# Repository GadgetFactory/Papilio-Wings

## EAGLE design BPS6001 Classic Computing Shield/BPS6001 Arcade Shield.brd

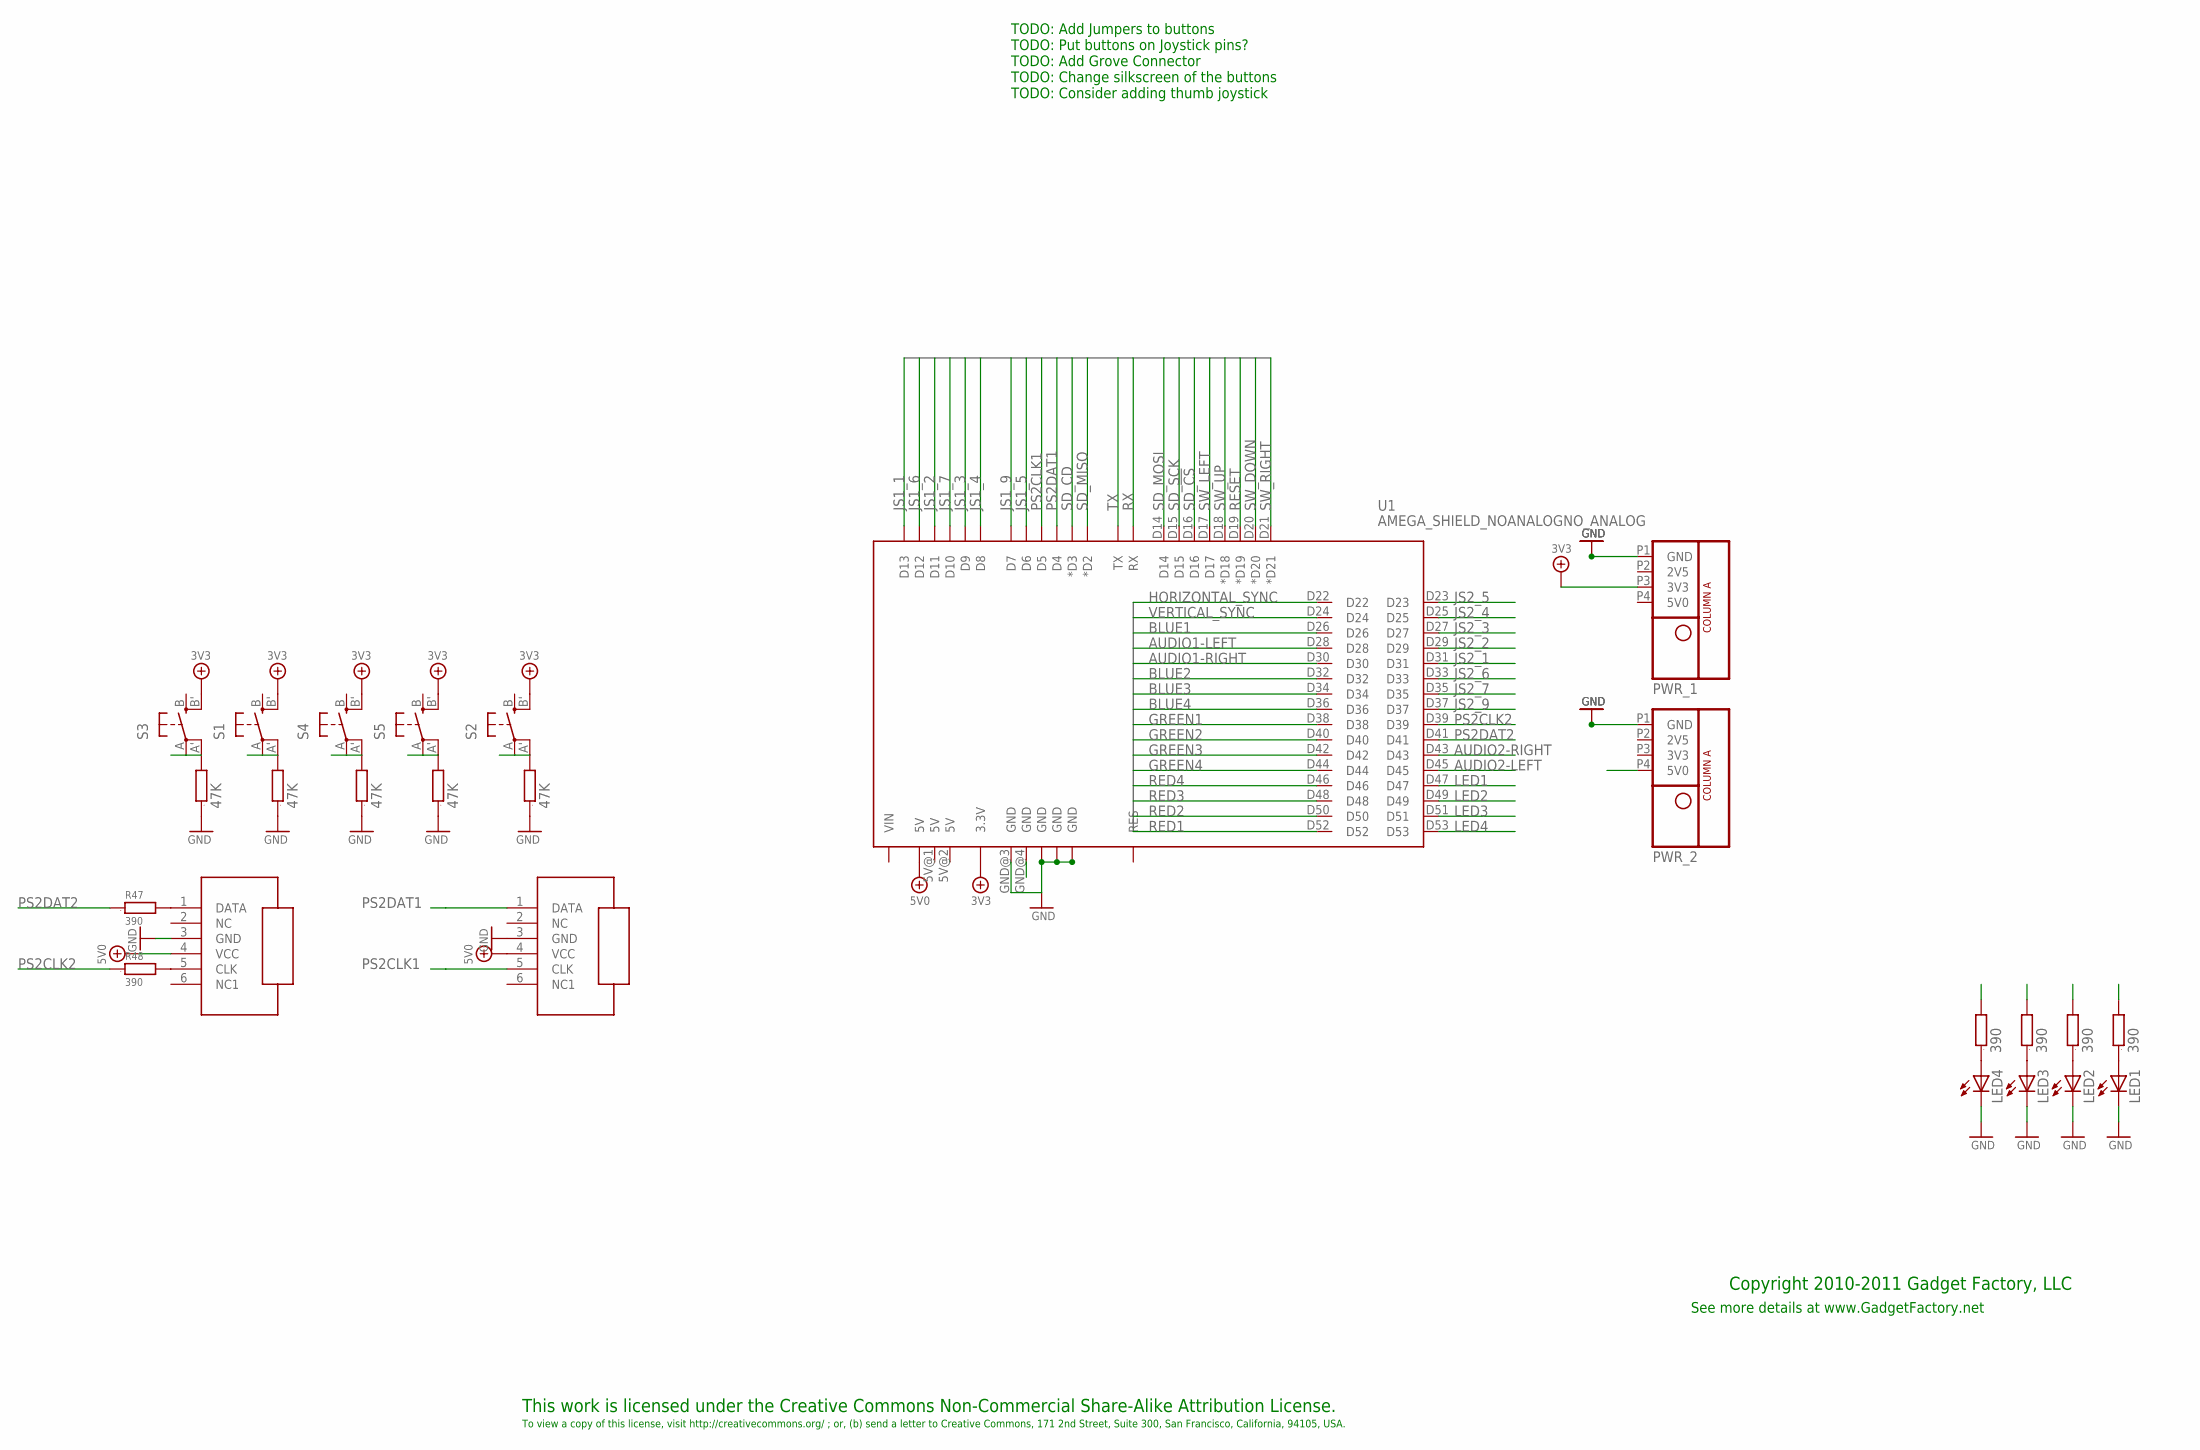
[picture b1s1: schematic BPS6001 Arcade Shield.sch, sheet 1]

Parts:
LED1, LED2, LED3, LED4: LEDCHIPLED_0603; CHIPLED_0603
LOGO1: BUTTERFLY_LOGO
PS2_A, PS2_B: CON_PS/2; PS/2
PWR_1, PWR_2: POWER_ONLYNOTEXT; POWER_NO_TEXT
R9, R10, R11, R17, R18: 47K; 0603
R26, R27, R43, R44, R47, R48: 390; 0603
S1, S2, S3, S4, S5: EVQQ2; EVQ-Q2
U1: AMEGA_SHIELD_NOANALOGNO_ANALOG; AMEGA_SHIELD_NOANALOG

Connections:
3V3: S1.B' (S1), S2.B' (S1), S3.B' (S1), S4.B' (S1), S5.B' (S1), U1.3.3V; also elsewhere on the board
5V0: PS2_A.4 (VCC), U1.5V@0 (5V)
5V0_PS2: PS2_B.4 (VCC), PWR_2.P4 (5V0)
AUDIO1-LEFT: U1.D28; also elsewhere on the board
AUDIO1-RIGHT: U1.D30; also elsewhere on the board
AUDIO2-LEFT: U1.D45; also elsewhere on the board
AUDIO2-RIGHT: U1.D43; also elsewhere on the board
BLUE1: U1.D26; also elsewhere on the board
BLUE2: U1.D32; also elsewhere on the board
BLUE3: U1.D34; also elsewhere on the board
BLUE4: U1.D36; also elsewhere on the board
GND: PS2_A.3 (GND), R9.1, R10.1, R11.1, R17.1, R18.1, U1.GND@0 (GND), U1.GND@1 (GND), U1.GND@2 (GND), U1.GND@3 (GND); also elsewhere on the board
GREEN1: U1.D38; also elsewhere on the board
GREEN2: U1.D40; also elsewhere on the board
GREEN3: U1.D42; also elsewhere on the board
GREEN4: U1.D44; also elsewhere on the board
HORIZONTAL_SYNC: U1.D22; also elsewhere on the board
JOY_3V3: PWR_1.P3 (3V3); also elsewhere on the board
JOY_GND: LED1.C, LED2.C, LED3.C, LED4.C, PS2_B.3 (GND), PWR_1.P1 (GND), PWR_2.P1 (GND), U1.GND@4 (GND); also elsewhere on the board
JS1_1: U1.D13; also elsewhere on the board
JS1_2: U1.D11; also elsewhere on the board
JS1_3: U1.D9; also elsewhere on the board
JS1_4: U1.D8; also elsewhere on the board
JS1_5: U1.D6; also elsewhere on the board
JS1_6: U1.D12; also elsewhere on the board
JS1_7: U1.D10; also elsewhere on the board
JS1_9: U1.D7; also elsewhere on the board
JS2_1: U1.D31; also elsewhere on the board
JS2_2: U1.D29; also elsewhere on the board
JS2_3: U1.D27; also elsewhere on the board
JS2_4: U1.D25; also elsewhere on the board
JS2_5: U1.D23; also elsewhere on the board
JS2_6: U1.D33; also elsewhere on the board
JS2_7: U1.D35; also elsewhere on the board
JS2_9: U1.D37; also elsewhere on the board
LED1: R26.2, U1.D47
LED2: R27.2, U1.D49
LED3: R43.2, U1.D51
LED4: R44.2, U1.D53
unnamed: LED4.A, R44.1
unnamed: LED3.A, R43.1
unnamed: LED2.A, R27.1
unnamed: LED1.A, R26.1
unnamed: PS2_B.1 (DATA), R47.2
unnamed: PS2_B.5 (CLK), R48.2
PS2CLK1: PS2_A.5 (CLK), U1.D5
PS2CLK2: R48.1, U1.D39
PS2DAT1: PS2_A.1 (DATA), U1.D4
PS2DAT2: R47.1, U1.D41
RED1: U1.D52; also elsewhere on the board
RED2: U1.D50; also elsewhere on the board
RED3: U1.D48; also elsewhere on the board
RED4: U1.D46; also elsewhere on the board
RESET: R11.2, S2.A, S2.A' (P1), U1.D19 (*D19)
RX: U1.RX; also elsewhere on the board
SD_!CS: U1.D16; also elsewhere on the board
SD_CD: U1.D3 (*D3); also elsewhere on the board
SD_MISO: U1.D2 (*D2); also elsewhere on the board
SD_MOSI: U1.D14; also elsewhere on the board
SD_SCK: U1.D15; also elsewhere on the board
SW_DOWN: R17.2, S4.A, S4.A' (P1), U1.D20 (*D20)
SW_LEFT: R9.2, S3.A, S3.A' (P1), U1.D17
SW_RIGHT: R18.2, S5.A, S5.A' (P1), U1.D21 (*D21)
SW_UP: R10.2, S1.A, S1.A' (P1), U1.D18 (*D18)
TX: U1.TX; also elsewhere on the board
VERTICAL_SYNC: U1.D24; also elsewhere on the board

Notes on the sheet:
This work is licensed under the Creative Commons Non-Commercial Share-Alike Attribution License.
To view a copy of this license, visit http://creativecommons.org/ ; or, (b) send a letter to Creative Commons, 171 2nd Street, Suite 300, San Francisco, California, 94105, USA.
Copyright 2010-2011 Gadget Factory, LLC
See more details at www.GadgetFactory.net
TODO: Add Jumpers to buttons TODO: Put buttons on Joystick pins? TODO: Add Grove Connector TODO: Change silkscreen of the buttons TODO: Consider adding thumb joystick

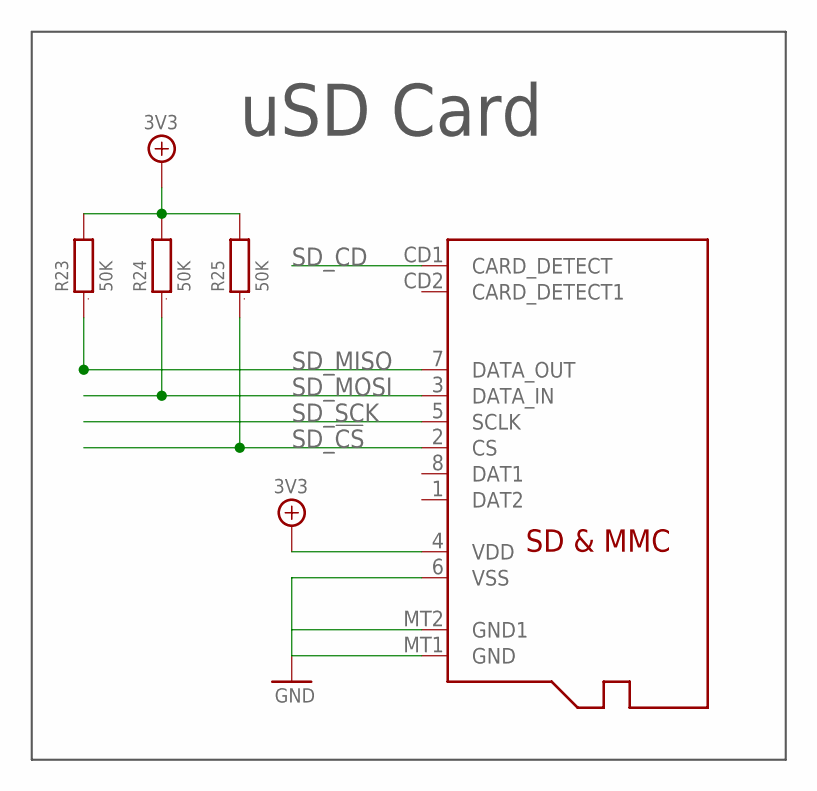
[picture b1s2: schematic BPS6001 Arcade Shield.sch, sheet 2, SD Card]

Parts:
R23, R24, R25: 50K; 0805
SD1: MICROSD

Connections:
3V3: R23.2, R24.2, R25.2, SD1.4 (VDD); also elsewhere on the board
GND: SD1.6 (VSS), SD1.MT1 (GND), SD1.MT2 (GND1); also elsewhere on the board
SD_!CS: R25.1, SD1.2 (CS); also elsewhere on the board
SD_CD: SD1.CD1 (CARD_DETECT); also elsewhere on the board
SD_MISO: R23.1, SD1.7 (DATA_OUT); also elsewhere on the board
SD_MOSI: R24.1, SD1.3 (DATA_IN); also elsewhere on the board
SD_SCK: SD1.5 (SCLK); also elsewhere on the board

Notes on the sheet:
uSD Card

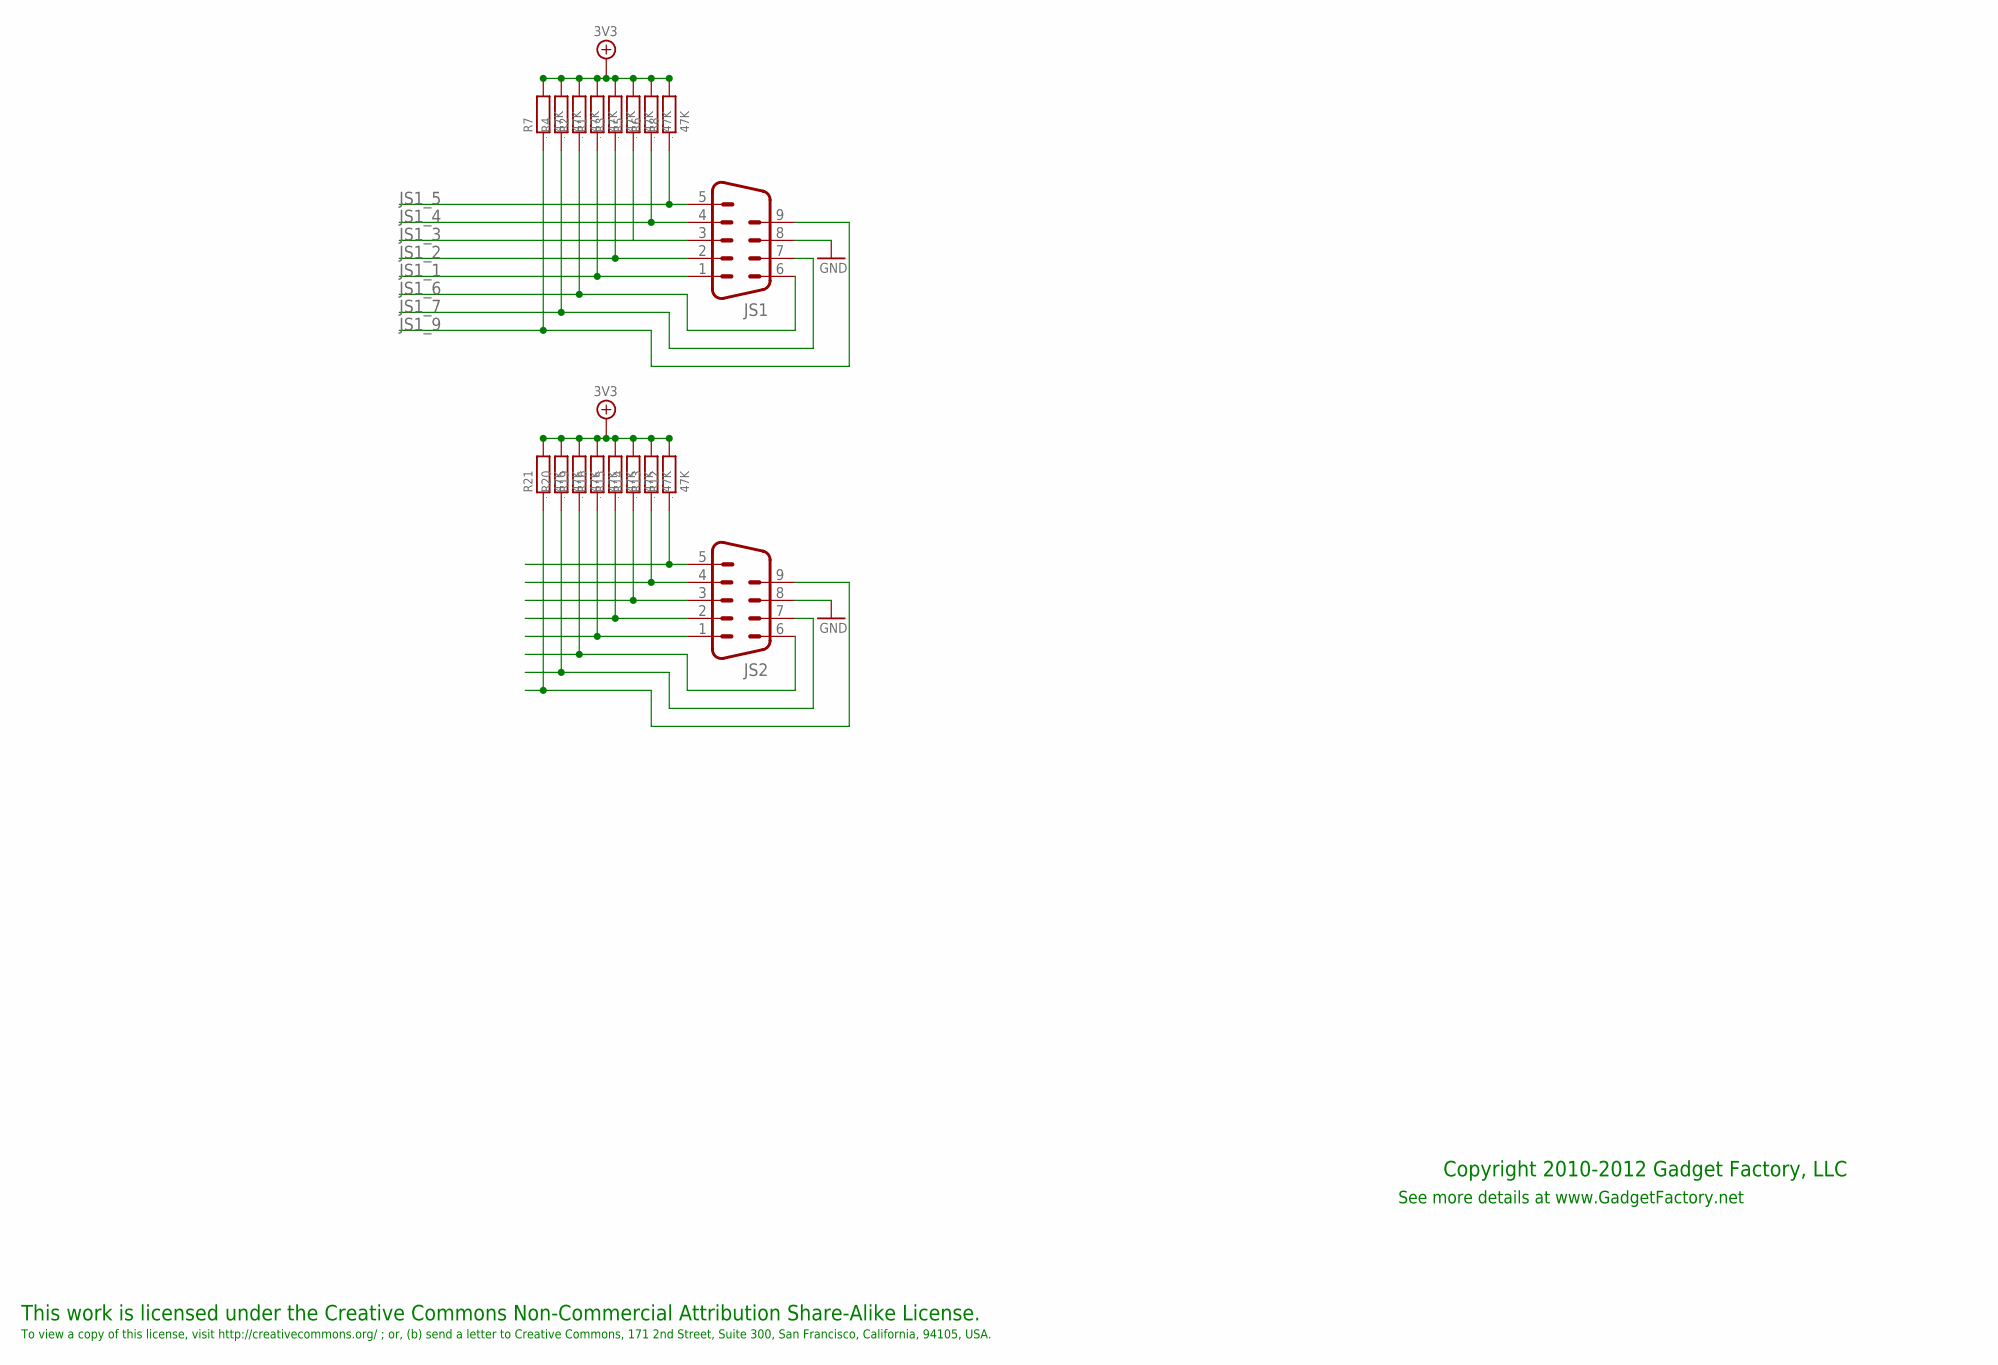
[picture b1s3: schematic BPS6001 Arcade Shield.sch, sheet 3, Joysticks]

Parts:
JS1, JS2: M09HP
R1, R2, R3, R4, R5, R6, R7, R8, R12, R13, R14, R15, R16, R19, R20, R21: 47K; 0603

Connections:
3V3: R1.2, R2.2, R3.2, R4.2, R5.2, R6.2, R7.2, R8.2; also elsewhere on the board
GND: JS1.8; also elsewhere on the board
JOY_3V3: R12.2, R13.2, R14.2, R15.2, R16.2, R19.2, R20.2, R21.2; also elsewhere on the board
JOY_GND: JS2.8; also elsewhere on the board
JS1_1: JS1.1, R1.1; also elsewhere on the board
JS1_2: JS1.2, R3.1; also elsewhere on the board
JS1_3: JS1.3, R5.1; also elsewhere on the board
JS1_4: JS1.4, R6.1; also elsewhere on the board
JS1_5: JS1.5, R8.1; also elsewhere on the board
JS1_6: JS1.6, R2.1; also elsewhere on the board
JS1_7: JS1.7, R4.1; also elsewhere on the board
JS1_9: JS1.9, R7.1; also elsewhere on the board
JS2_1: JS2.1, R16.1; also elsewhere on the board
JS2_2: JS2.2, R15.1; also elsewhere on the board
JS2_3: JS2.3, R14.1; also elsewhere on the board
JS2_4: JS2.4, R13.1; also elsewhere on the board
JS2_5: JS2.5, R12.1; also elsewhere on the board
JS2_6: JS2.6, R19.1; also elsewhere on the board
JS2_7: JS2.7, R20.1; also elsewhere on the board
JS2_9: JS2.9, R21.1; also elsewhere on the board

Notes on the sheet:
This work is licensed under the Creative Commons Non-Commercial Attribution Share-Alike License.
To view a copy of this license, visit http://creativecommons.org/ ; or, (b) send a letter to Creative Commons, 171 2nd Street, Suite 300, San Francisco, California, 94105, USA.
Copyright 2010-2012 Gadget Factory, LLC
See more details at www.GadgetFactory.net

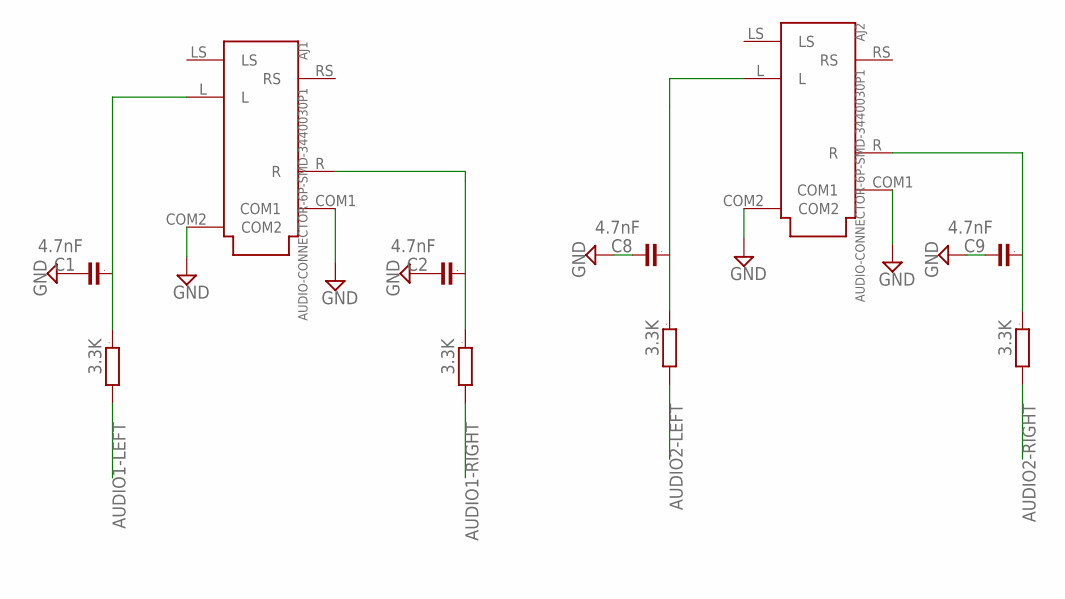
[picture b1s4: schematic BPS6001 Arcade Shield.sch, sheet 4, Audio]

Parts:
AJ1, AJ2: AUDIO-CONNECTOR-6P-SMD-3440030P1; 6P-SMD-3.5
C1, C2, C8, C9: 4.7nF; 0603
R22, R28, R45, R46: 3.3K; 0603

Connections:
AUDIO1-LEFT: R22.2; also elsewhere on the board
AUDIO1-RIGHT: R28.2; also elsewhere on the board
AUDIO2-LEFT: R45.2; also elsewhere on the board
AUDIO2-RIGHT: R46.2; also elsewhere on the board
GND: AJ1.COM1, AJ1.COM2, C1.2, C2.2; also elsewhere on the board
JOY_GND: AJ2.COM1, AJ2.COM2, C8.2, C9.2; also elsewhere on the board
unnamed: AJ2.L, C8.1, R45.1
unnamed: AJ1.L, C1.1, R22.1
unnamed: AJ2.R, C9.1, R46.1
unnamed: AJ1.R, C2.1, R28.1

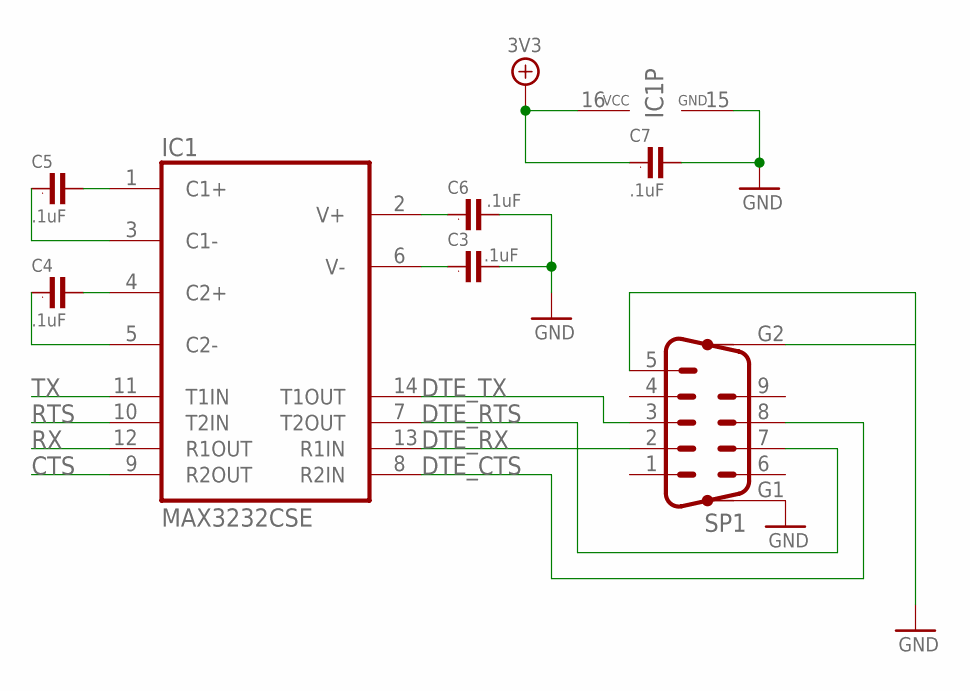
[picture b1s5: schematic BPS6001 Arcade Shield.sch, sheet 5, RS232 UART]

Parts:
C3, C4, C5, C6, C7: .1uF; 0805
IC1: MAX3232CSE; SO16
SP1: M09HP

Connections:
3V3: C7.1, IC1.16 (VCC); also elsewhere on the board
CTS: IC1.9 (R2OUT)
DTE_CTS: IC1.8 (R2IN), SP1.8
DTE_RTS: IC1.7 (T2OUT), SP1.7
DTE_RX: IC1.13 (R1IN), SP1.2
DTE_TX: IC1.14 (T1OUT), SP1.3
GND: C3.2, C6.2, C7.2, IC1.15 (GND), SP1.5, SP1.G1, SP1.G2; also elsewhere on the board
unnamed: C6.1, IC1.2 (V+)
unnamed: C3.1, IC1.6 (V-)
unnamed: C5.2, IC1.1 (C1+)
unnamed: C4.2, IC1.4 (C2+)
unnamed: C5.1, IC1.3 (C1-)
unnamed: C4.1, IC1.5 (C2-)
RTS: IC1.10 (T2IN)
RX: IC1.12 (R1OUT); also elsewhere on the board
TX: IC1.11 (T1IN); also elsewhere on the board

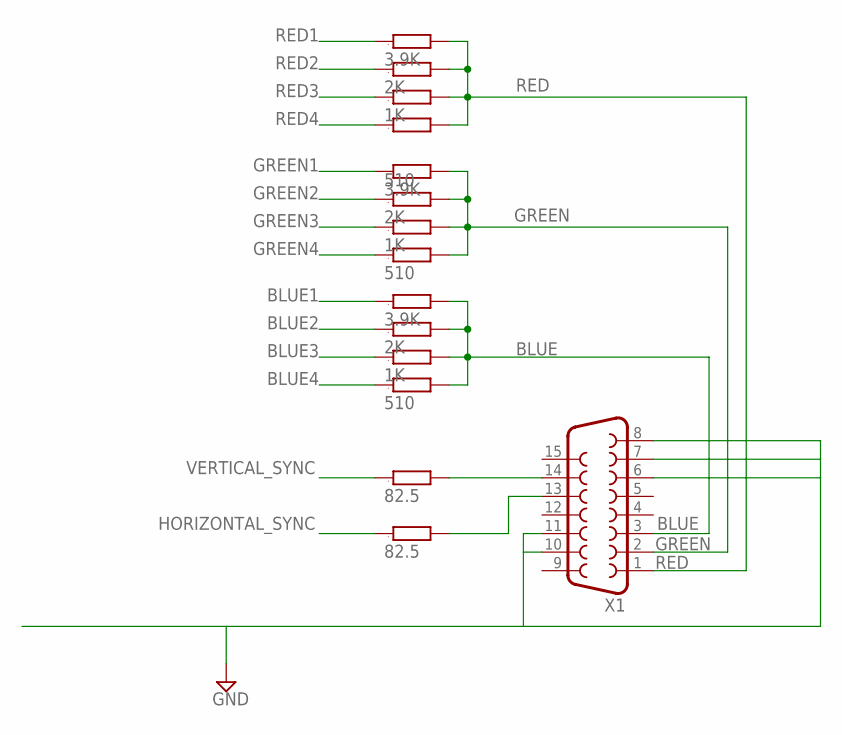
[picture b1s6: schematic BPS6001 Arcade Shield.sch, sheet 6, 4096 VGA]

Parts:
R29, R30: 82.5; 0603
R31, R35, R42: 3.9K; 0603
R32, R36, R41: 2K; 0603
R33, R37, R40: 1K; 0603
R34, R38, R39: 510; 0603
X1: F15HDH; HDF15H

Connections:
BLUE: R31.2, R32.2, R33.2, R34.2, X1.3
BLUE1: R31.1; also elsewhere on the board
BLUE2: R32.1; also elsewhere on the board
BLUE3: R33.1; also elsewhere on the board
BLUE4: R34.1; also elsewhere on the board
GND: X1.6, X1.7, X1.8, X1.10, X1.11; also elsewhere on the board
GREEN: R35.2, R36.2, R37.2, R38.2, X1.2
GREEN1: R35.1; also elsewhere on the board
GREEN2: R36.1; also elsewhere on the board
GREEN3: R37.1; also elsewhere on the board
GREEN4: R38.1; also elsewhere on the board
HORIZONTAL_SYNC: R29.1; also elsewhere on the board
unnamed: R29.2, X1.13
unnamed: R30.2, X1.14
RED: R39.2, R40.2, R41.2, R42.2, X1.1
RED1: R42.1; also elsewhere on the board
RED2: R41.1; also elsewhere on the board
RED3: R40.1; also elsewhere on the board
RED4: R39.1; also elsewhere on the board
VERTICAL_SYNC: R30.1; also elsewhere on the board

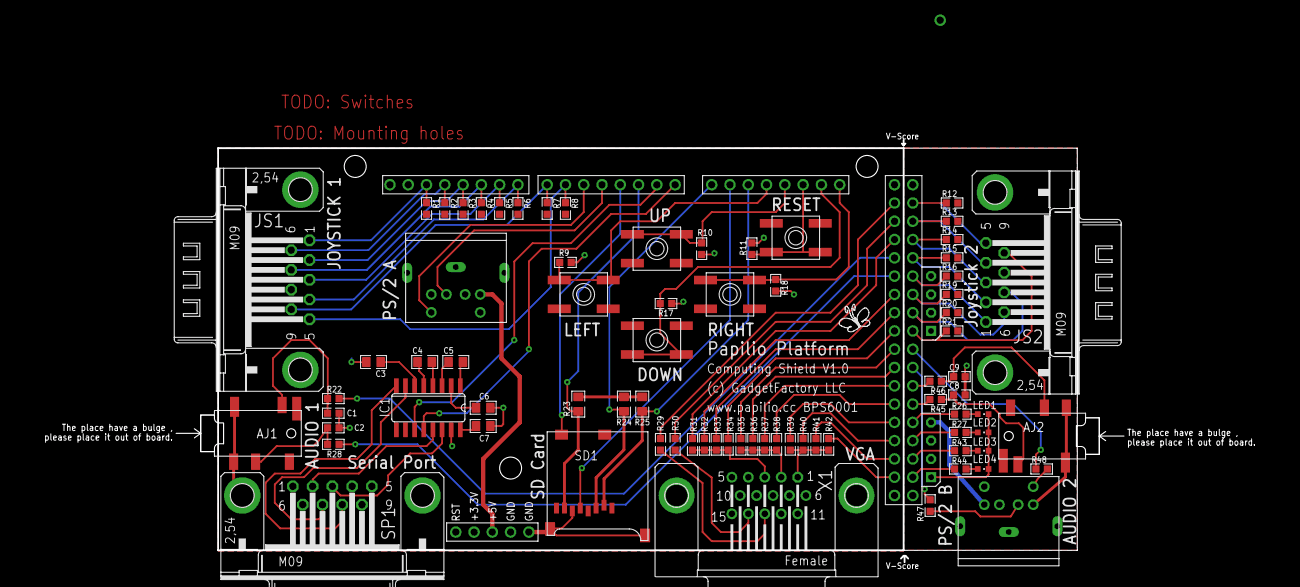
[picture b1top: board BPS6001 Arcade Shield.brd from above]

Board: 2 copper layers, 119.4 x 55.9 mm, 83 parts (0 on the bottom side), 85 nets.

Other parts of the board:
U$1, U$2, U$3: STAND-OFF-TIGHT

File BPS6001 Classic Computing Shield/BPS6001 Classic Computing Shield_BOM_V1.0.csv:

Qty-1,Part References,Value,Package,Mfg Part Num,Mfg Name,VID,Vendor Part Num,Description,Pkg Code,XREF
1,"GROVE1",,CONNECTOR_4P-LEADED-2.0,ACC39145O,Seeed Studio,SD,ACC39145O,Seeed Universal Grove Connector,*,REF178
4,"LED1, LED2, LED3, LED4",,CHIPLED_0603,LTST-C190GKT,LITE-ON INC (VA),DK,160-1183-1-ND,LED GREEN CLEAR 0603 SMD,603,REF176
1,"CFG1",,JP5Q,M20-9720545,Harwin,DK,952-1927-ND,2X5POS DIL VERTICAL PIN HEADER,*,REF177
5,"S1, S2, S3, S4, S5",,EVQ-Q2,PTS525SM10SMTR LFS,C&K Components,DK,CKN9104CT-ND,SWITCH TACTILE SPST-NO 0.05A 12V,*,REF119
5,"C3, C4, C5, C6, C7",.1uF,0805,GRM21BR71E104KA01L,MURATA ELECTRONICS (VA),DK,490-1673-1-ND,CAP CER .1UF 25V 10% X7R 0805,805,REF97
3,"R33, R37, R40",1K,0603,RMCF0603JT1K00,StackPole,DK,RMCF0603JT1K00CT-ND,RES 1K OHM 1/10W 5% 0603,603,REF140
3,"R32, R36, R41",2K,0603,RMCF0603JT2K00,Stackpole,DK,RMCF0603JT2K00CT-ND,RES 2K OHM 1/10W 5% 0603,603,REF172
4,"R22, R28, R45, R46",3.3K,0603,RMCF0603JT3K30,Stackpole,DK,RMCF0603JT3K30CT-ND,RES 3.3K OHM 1/10W 5% 0603,603,REF168
3,"R31, R35, R42",3.9K,0603,RMCF0603JT3K90,Stackpole,DK,RMCF0603JT3K90CT-ND,RES 3.9K OHM 1/10W 5% 0603,603,REF171
24,"R1, R2, R3, R4, R5, R6, R7, R8, R9, R10, R11, R12, R13, R14, R15, R16, R17, R18, R19, R20, R21, R23, R24, R25",47K,0603,RMCF0603JT47K0,Stackpole,DK,RMCF0603JT47K0CT-ND,RES 47K OHM 1/10W 5% 0603,603,REF167
2,"R29, R30",82.5,0603,RMCF0603FT82R5,Stackpole,DK,RMCF0603FT82R5CT-ND,RES 82.5 OHM 1/10W 1% 0603,603,REF170
6,"R26, R27, R43, R44, R47, R48",390,0603,RMCF0603JT390R,StackPole,DK,RMCF0603JT390RCT-ND,RES 390 OHM 1/10W 5% 0603,603,REF141
3,"R34, R38, R39",510,0603,RMCF0603JT510R,Stackpole,DK,RMCF0603JT510RCT-ND,RES 510 OHM 1/10W 5% 0603,603,REF174
4,"C1, C2, C8, C9",4700pF,0603,C0603C472J5RACTU,Kemet,DK,399-1088-1-ND,CAP CER 4700PF 50V 5% X7R 0603 - Audio cap,603,REF175
2,"AJ1, AJ2",AUDIO-CONNECTOR-6P-SMD-3440030P1,6P-SMD-3.5,3440030P1,Seeed Studio,SD,3440030P1,6P-SMD-3.5 - Audio Connector,*,REF183
2,"PS2_A, PS2_B",CON_PS/2,PS/2,MD-60S,CUI,DK,CP-2460-ND,CONN MINIDIN RECPT UNSHIELD 6POS - PS/2,*,REF180
1,"IC1",MAX3232CSE,SO16,MAX3232ECDR,Texas Instruments,DK,296-19851-1-ND,IC RS232 3V5.5V 15KVESD 16-SOIC - Max3232,SO16,REF184
1,"SD1",MICROSD,MICROSD,101-00660-68-6,Amphenol,DK,101-00660-68-6-1-ND,CONN MINI MICRO-SD 8PIN PCB GOLD - MicroSD,*,REF181
3,"JS1, JS2, SP1",Serial Port,M09HP,10090097-P094VLF,FCI,DK,609-4003-ND,DSUB R/A US 9POS PIN - Serial Port,*,REF179
1,"X1",VGA,HDF15H,1-1734530-1,TE Connectivity,DK,A35116-ND,CONN HD D-SUB RCPT R/A 15POS - VGA Connector,*,REF182

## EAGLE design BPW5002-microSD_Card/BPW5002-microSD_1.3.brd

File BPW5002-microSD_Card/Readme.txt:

BPW5002 Micro SD Wing Manufacturing Package - Current Version 1.3

Special assembly instructions:
-Use RED for the PCB color.

CHANGELOG
8/21/2014 Version 1.0

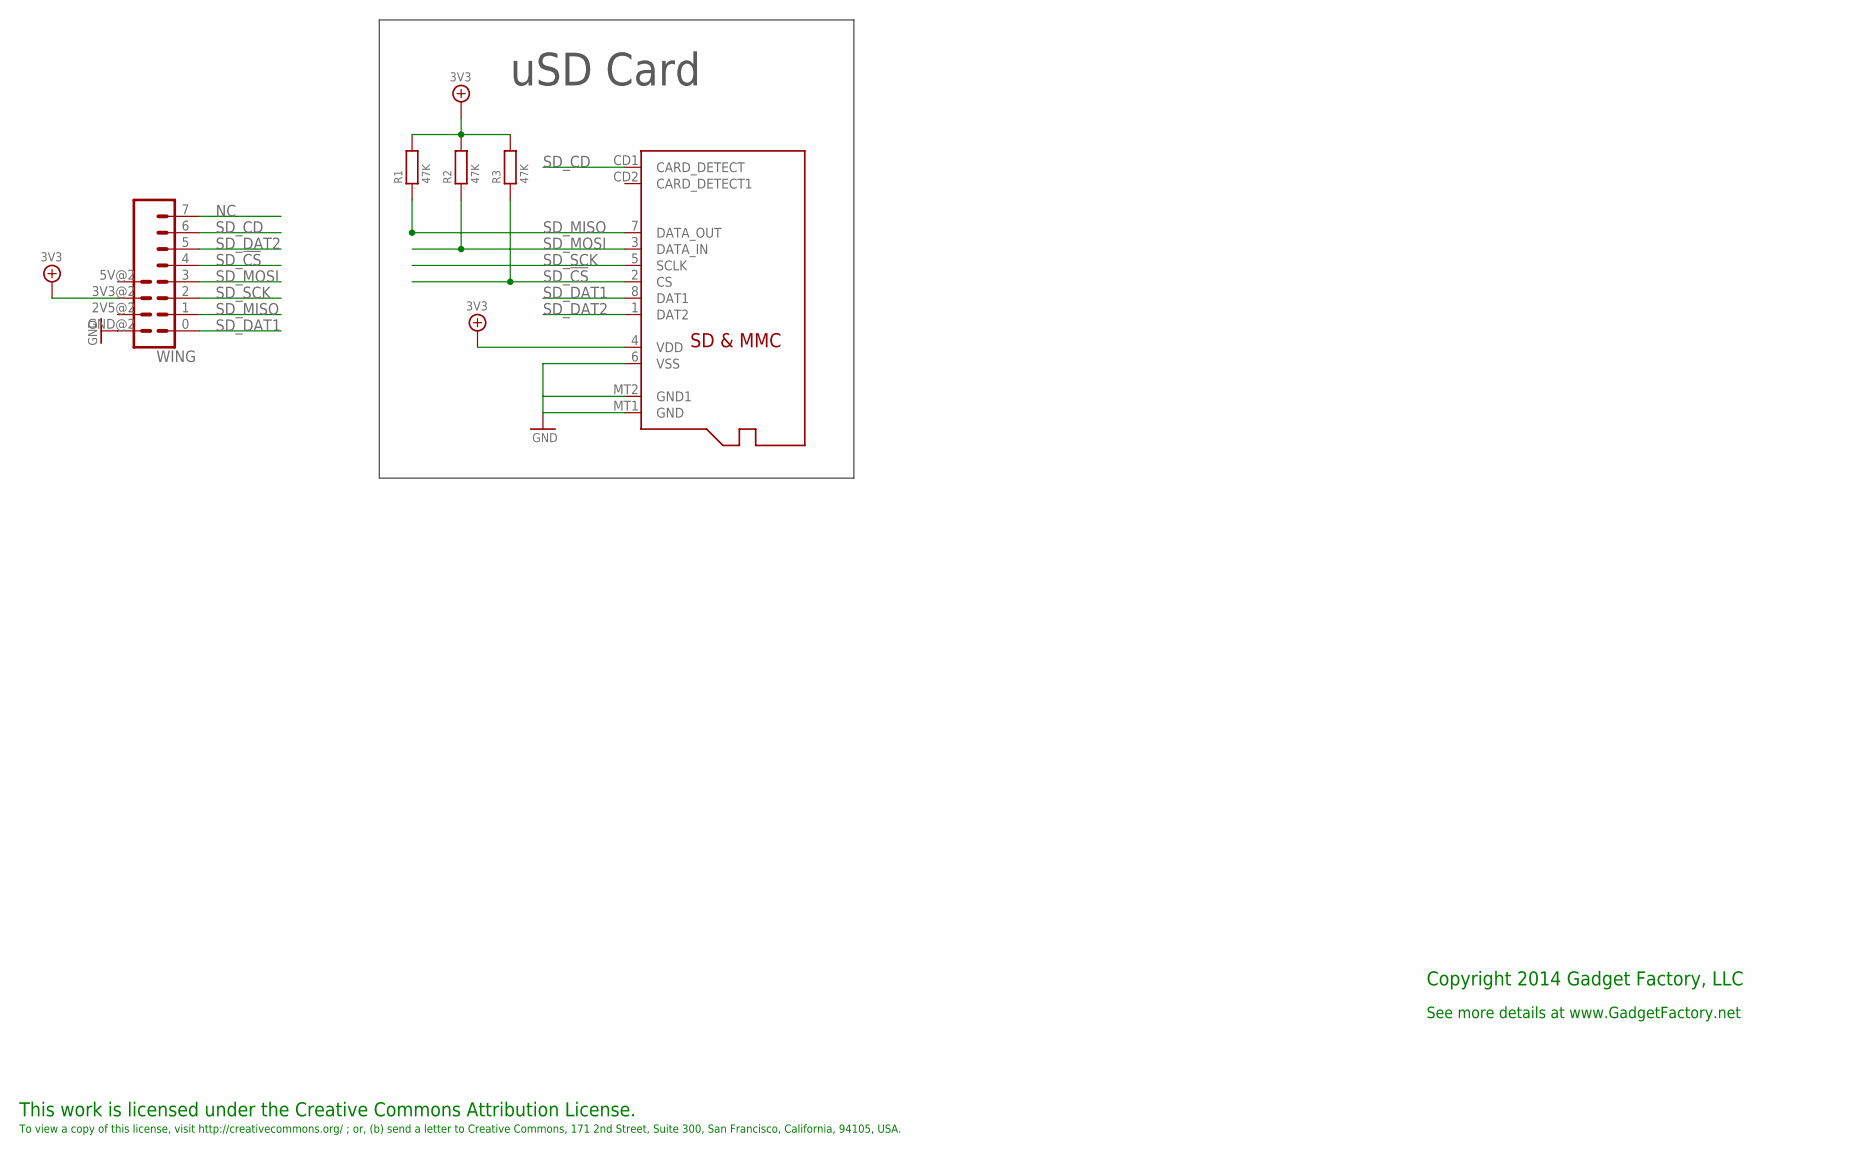
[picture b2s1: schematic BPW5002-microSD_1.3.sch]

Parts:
LOGO2: BUTTERFLY_LOGO
R1, R2, R3: 47K; 0805; PARTNO RMCF0805JT47K0
SD1: MICROSD; PARTNO 101-00660-68-6
WING: WING8WING8_NOHOLES; WINGSIDE_8BIT_NOHOLES; PARTNO 68001-112HLF

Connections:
3V3: R1.2, R2.2, R3.2, SD1.4 (VDD), WING.3V3@2 (3V3)
GND: SD1.6 (VSS), SD1.MT1 (GND), SD1.MT2 (GND1), WING.GND@2 (GND)
NC: WING.7 (8)
SD_!CS: R3.1, SD1.2 (CS), WING.4 (5)
SD_CD: SD1.CD1 (CARD_DETECT), WING.6 (7)
SD_DAT1: SD1.8 (DAT1), WING.0 (1)
SD_DAT2: SD1.1 (DAT2), WING.5 (6)
SD_MISO: R1.1, SD1.7 (DATA_OUT), WING.1 (2)
SD_MOSI: R2.1, SD1.3 (DATA_IN), WING.3 (4)
SD_SCK: SD1.5 (SCLK), WING.2 (3)

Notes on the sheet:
This work is licensed under the Creative Commons Attribution License.
To view a copy of this license, visit http://creativecommons.org/ ; or, (b) send a letter to Creative Commons, 171 2nd Street, Suite 300, San Francisco, California, 94105, USA.
Copyright 2014 Gadget Factory, LLC
See more details at www.GadgetFactory.net
uSD Card

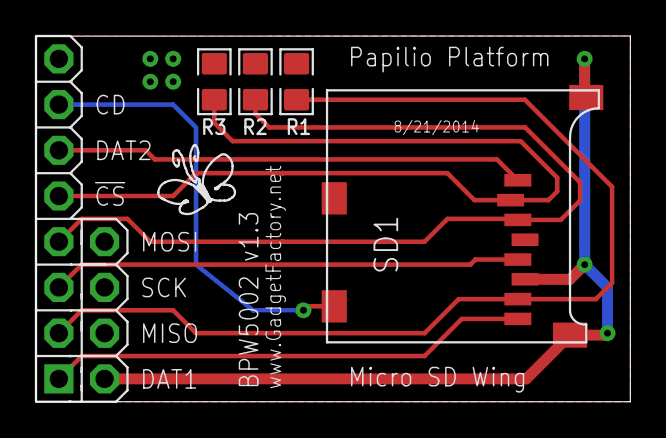
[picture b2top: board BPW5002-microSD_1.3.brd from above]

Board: 2 copper layers, 33.0 x 20.3 mm, 6 parts (0 on the bottom side), 9 nets.

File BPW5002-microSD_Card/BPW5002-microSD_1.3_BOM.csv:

Qty-1,Part References,Value,Package,Mfg Part Num,Mfg Name,VID,Vendor Part Num,Description,Pkg Code,XREF
3,"R1, R2, R3",47K,0805,RMCF0805JT47K0,Stackpole Electronics Inc,DK,RMCF0805JT47K0CT-ND,RES 47K OHM 1/8W 5% 0805 SMD,805,REF109
1,"SD1",MICROSD,MICROSD,101-00660-68-6,Amphenol,DK,101-00660-68-6-1-ND,CONN MINI MICRO-SD 8PIN PCB GOLD - MicroSD,*,REF181
1,"WING",WING8WING8_NOHOLES,WINGSIDE_8BIT_NOHOLES,68001-112HLF,FCI,DK,609-3275-ND,Papilio 8-bit Wing header. 12 Male Pin Headers to be split into 8 pins and 4 pins.,WINGSIDE_8BIT_NOHOLES,REF193
